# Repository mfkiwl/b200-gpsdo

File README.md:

USRP B200 GPSDO
===============

TODO

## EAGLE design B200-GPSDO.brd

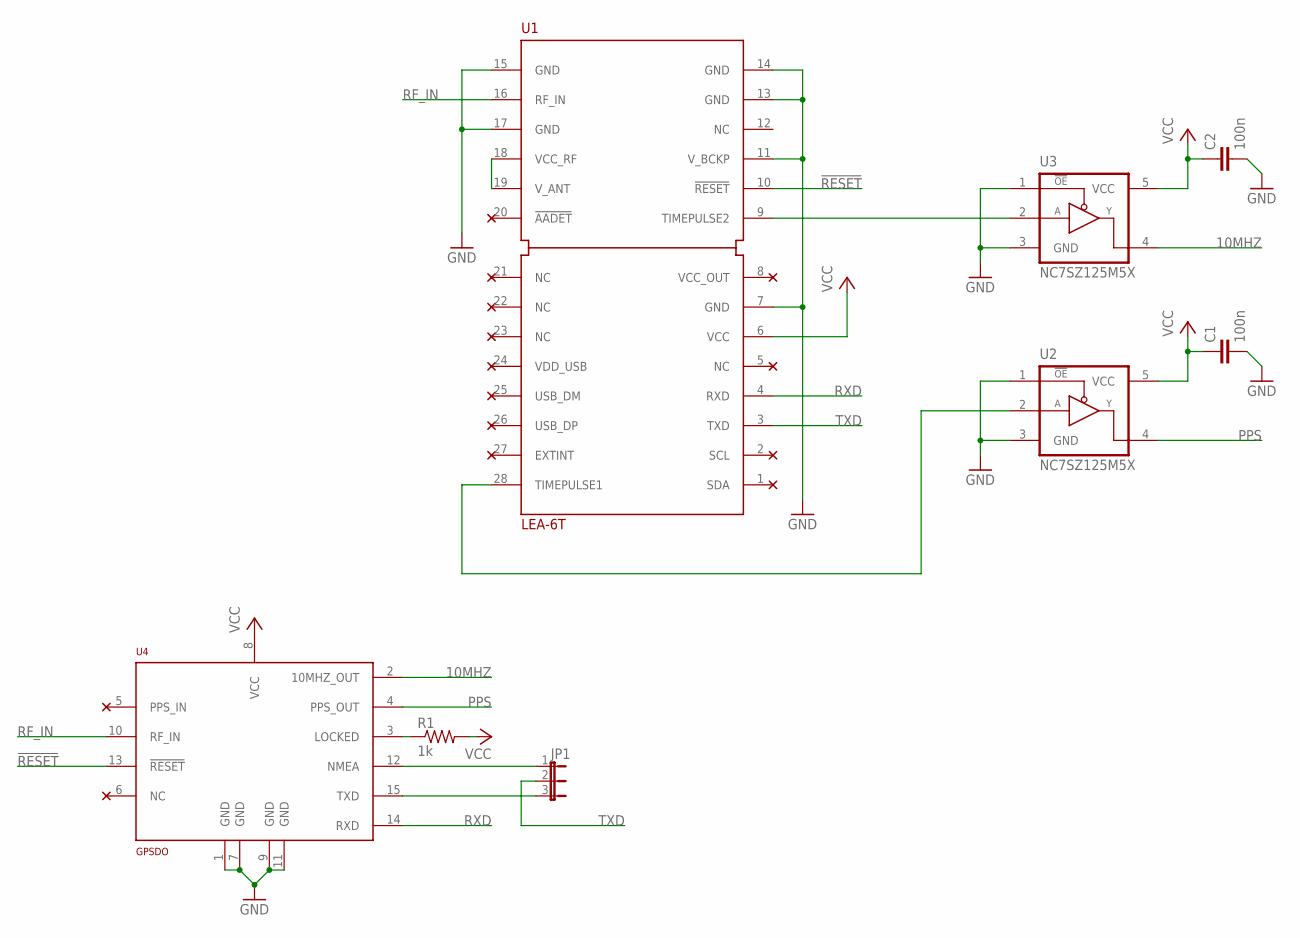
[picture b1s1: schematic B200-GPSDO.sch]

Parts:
C1, C2: 100n; C0805
JP1: JP2E; JP2
R1: 1k; R0805
U1: LEA-6T; LEA
U2, U3: NC7SZ125M5X; SOT-23-5
U4: GPSDO

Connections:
10MHZ: U3.4 (Y), U4.2 (10MHZ_OUT)
!RESET: U1.10 (!RESET), U4.13 (!RESET)
GND: C1.2, C2.2, U1.7 (GND), U1.11 (V_BCKP), U1.13 (GND), U1.14 (GND), U1.15 (GND), U1.17 (GND), U2.1 (OE#), U2.3 (GND), U3.1 (OE#), U3.3 (GND), U4.1 (GND), U4.7 (GND), U4.9 (GND), U4.11 (GND)
unnamed: U1.18 (VCC_RF), U1.19 (V_ANT)
unnamed: U1.9 (TIMEPULSE2), U3.2 (A)
unnamed: U1.28 (TIMEPULSE1), U2.2 (A)
unnamed: R1.1, U4.3 (LOCKED)
unnamed: JP1.1, U4.12 (NMEA)
unnamed: JP1.3, U4.15 (TXD)
PPS: U2.4 (Y), U4.4 (PPS_OUT)
RF_IN: U1.16 (RF_IN), U4.10 (RF_IN)
RXD: U1.4 (RXD), U4.14 (RXD)
TXD: JP1.2, U1.3 (TXD)
VCC: C1.1, C2.1, R1.2, U1.6 (VCC), U2.5 (VCC), U3.5 (VCC), U4.8 (VCC)

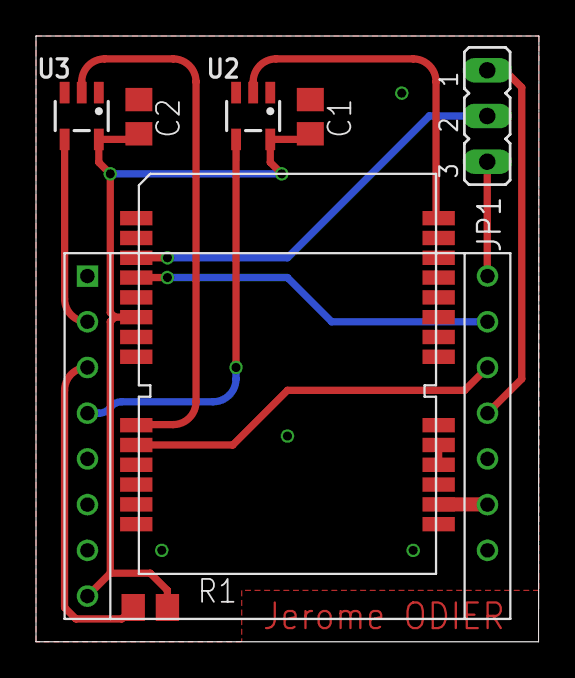
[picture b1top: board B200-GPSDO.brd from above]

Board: 2 copper layers, 27.9 x 33.7 mm, 8 parts (0 on the bottom side), 14 nets.

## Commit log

2016-09-15 updat
